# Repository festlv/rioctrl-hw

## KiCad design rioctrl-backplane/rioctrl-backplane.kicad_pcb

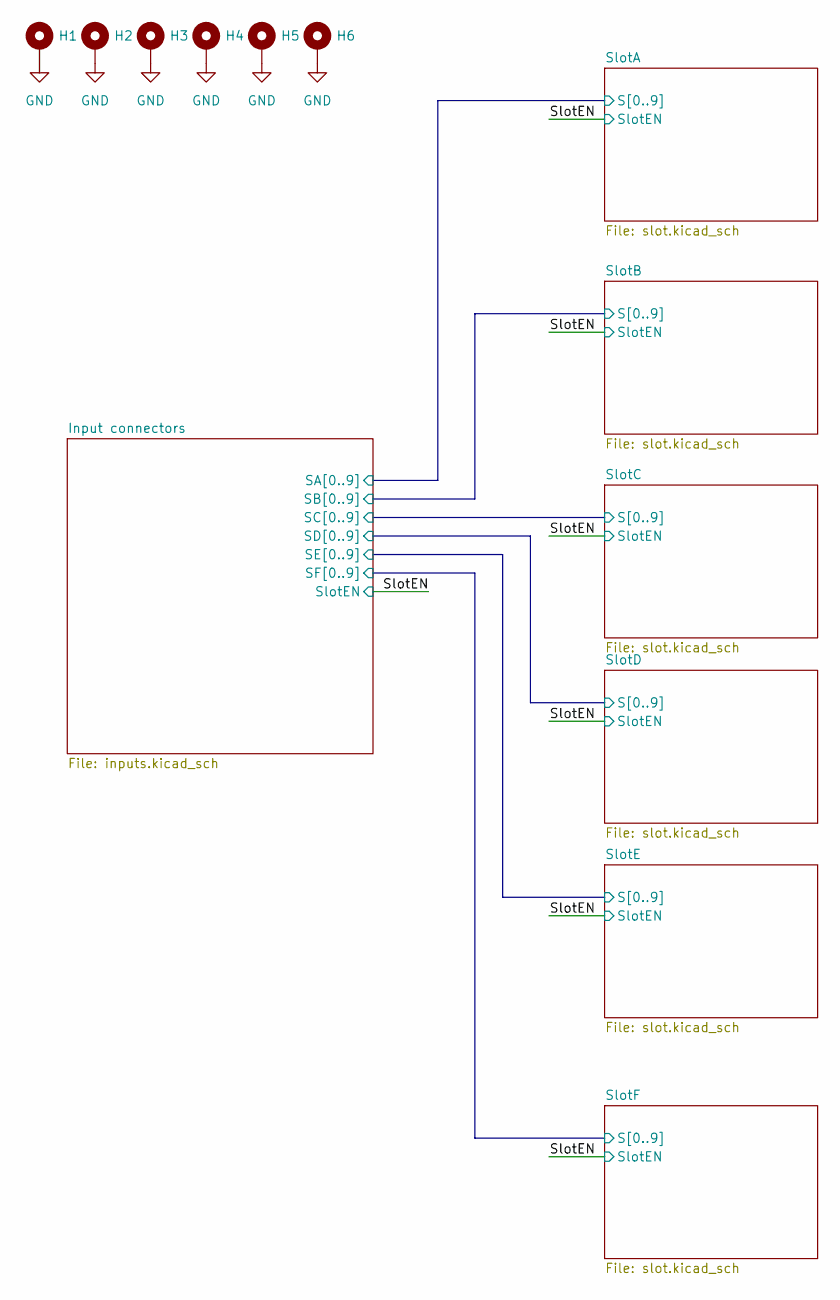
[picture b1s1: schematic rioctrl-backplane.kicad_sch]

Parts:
H1, H2, H3, H4, H5, H6: MH_3.2mm; MountingHole_3.2mm_M3_Pad_Via

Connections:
GND: H1.1, H2.1, H3.1, H4.1, H5.1, H6.1; also elsewhere on the board

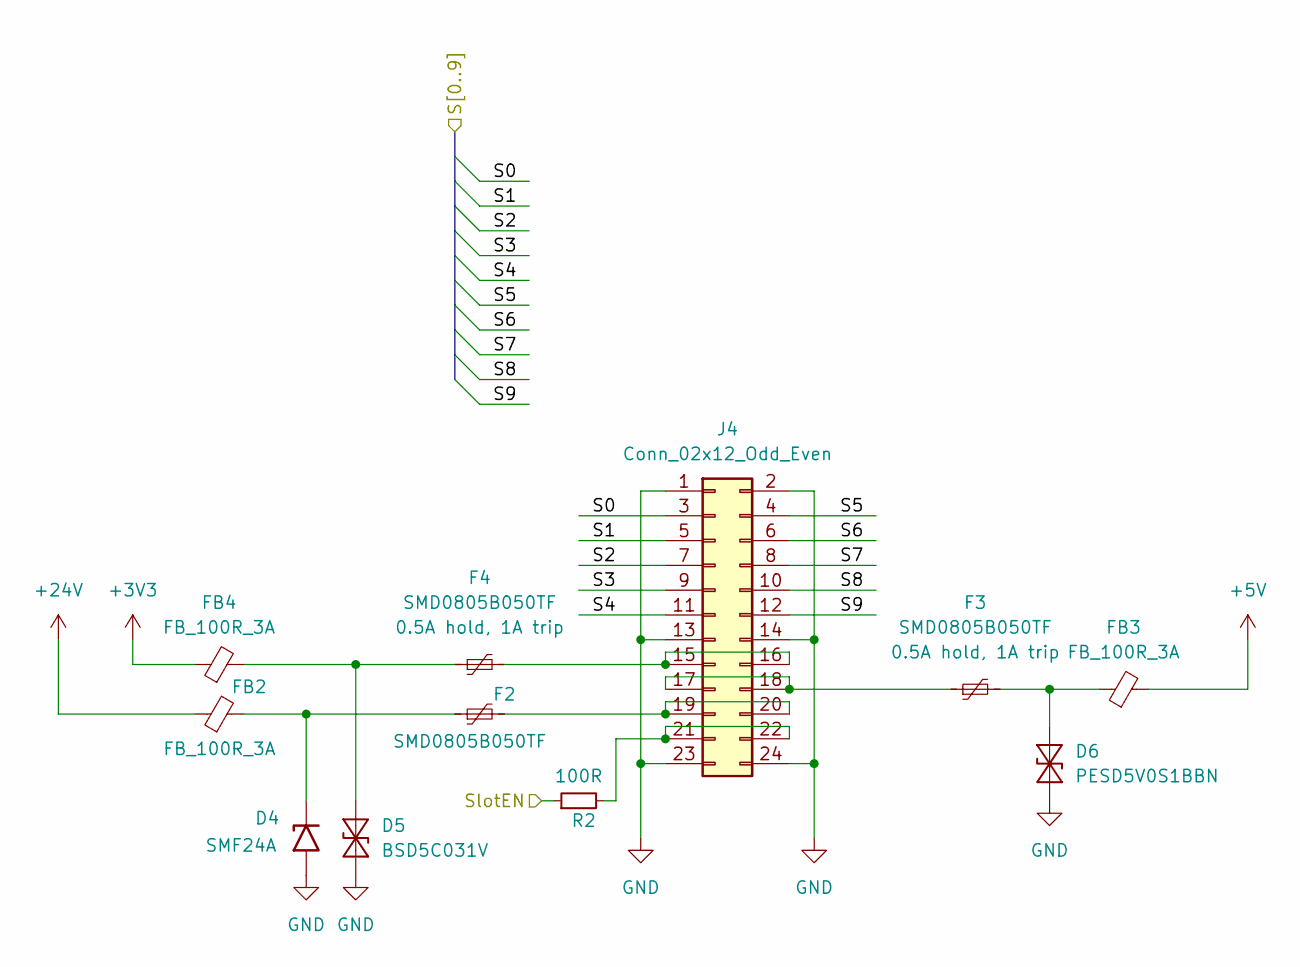
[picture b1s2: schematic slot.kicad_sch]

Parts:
D4: SMF24A; D_SOD-123F; MPN SMF24A; LCSC# C169430
D5: BSD5C031V; D_SOD-523; MPN BSD5C031V; LCSC# C151984
D6: PESD5V0S1BBN; D_SOD-523; MPN PESD5V0S1BBN; LCSC# C314264
F2, F3, F4: SMD0805B050TF; Fuse_0805_2012Metric; MPN SMD0805B050TF; LCSC# C269104
FB2, FB3, FB4: FB_100R_3A; L_0603_1608Metric; MPN UPZ1608E101-3R0TF; LCSC# C96995
J4: Conn_02x12_Odd_Even; PinSocket_2x12_P2.54mm_Vertical_SMD
R2: 100R; R_0603_1608Metric

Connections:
+3V3: FB4.1; also elsewhere on the board
+5V: FB3.2; also elsewhere on the board
+24V: FB2.1; also elsewhere on the board
/Input connectors/SB0: J4.3; also elsewhere on the board
/Input connectors/SB1: J4.5; also elsewhere on the board
/Input connectors/SB2: J4.7; also elsewhere on the board
/Input connectors/SB3: J4.9; also elsewhere on the board
/Input connectors/SB4: J4.11; also elsewhere on the board
/Input connectors/SB5: J4.4; also elsewhere on the board
/Input connectors/SB6: J4.6; also elsewhere on the board
/Input connectors/SB7: J4.8; also elsewhere on the board
/Input connectors/SB8: J4.10; also elsewhere on the board
/Input connectors/SB9: J4.12; also elsewhere on the board
/SlotEN: R2.1; also elsewhere on the board
GND: D4.2 (A2), D5.1 (A1), D6.2 (A2), J4.1, J4.2, J4.13, J4.14, J4.23, J4.24; also elsewhere on the board
unnamed: D5.2 (A2), F4.1, FB4.2
unnamed: F4.2, J4.15, J4.16
unnamed: J4.21, J4.22, R2.2

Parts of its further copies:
D1, D7, D10, D13, D16: SMF24A; D_SOD-123F; MPN SMF24A; LCSC# C169430
D2, D8, D11, D14, D17: BSD5C031V; D_SOD-523; MPN BSD5C031V; LCSC# C151984
D3, D9, D12, D15, D18: PESD5V0S1BBN; D_SOD-523; MPN PESD5V0S1BBN; LCSC# C314264
F1, F5, F6, F7, F8, F9, F10, F11, F12, F13, F14, F15, F16, F17, F18: SMD0805B050TF; Fuse_0805_2012Metric; MPN SMD0805B050TF; LCSC# C269104
FB1, FB5, FB6, FB7, FB8, FB9, FB10, FB11, FB12, FB13, FB14, FB15, FB16, FB17, FB18: FB_100R_3A; L_0603_1608Metric; MPN UPZ1608E101-3R0TF; LCSC# C96995
J3, J5, J6, J7, J8: Conn_02x12_Odd_Even; PinSocket_2x12_P2.54mm_Vertical_SMD
R1, R3, R4, R5, R6: 100R; R_0603_1608Metric

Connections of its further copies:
+3V3: FB1.1, FB7.1, FB10.1, FB13.1, FB16.1; also elsewhere on the board
+5V: FB6.2, FB9.2, FB12.2, FB15.2, FB18.2; also elsewhere on the board
+24V: FB5.1, FB8.1, FB11.1, FB14.1, FB17.1; also elsewhere on the board
/Input connectors/SA0: J3.3; also elsewhere on the board
/Input connectors/SA1: J3.5; also elsewhere on the board
/Input connectors/SA2: J3.7; also elsewhere on the board
/Input connectors/SA3: J3.9; also elsewhere on the board
/Input connectors/SA4: J3.11; also elsewhere on the board
/Input connectors/SA5: J3.4; also elsewhere on the board
/Input connectors/SA6: J3.6; also elsewhere on the board
/Input connectors/SA7: J3.8; also elsewhere on the board
/Input connectors/SA8: J3.10; also elsewhere on the board
/Input connectors/SA9: J3.12; also elsewhere on the board
/Input connectors/SC0: J5.3; also elsewhere on the board
/Input connectors/SC1: J5.5; also elsewhere on the board
/Input connectors/SC2: J5.7; also elsewhere on the board
/Input connectors/SC3: J5.9; also elsewhere on the board
/Input connectors/SC4: J5.11; also elsewhere on the board
/Input connectors/SC5: J5.4; also elsewhere on the board
/Input connectors/SC6: J5.6; also elsewhere on the board
/Input connectors/SC7: J5.8; also elsewhere on the board
/Input connectors/SC8: J5.10; also elsewhere on the board
/Input connectors/SC9: J5.12; also elsewhere on the board
/Input connectors/SD0: J6.3; also elsewhere on the board
/Input connectors/SD1: J6.5; also elsewhere on the board
/Input connectors/SD2: J6.7; also elsewhere on the board
/Input connectors/SD3: J6.9; also elsewhere on the board
/Input connectors/SD4: J6.11; also elsewhere on the board
/Input connectors/SD5: J6.4; also elsewhere on the board
/Input connectors/SD6: J6.6; also elsewhere on the board
/Input connectors/SD7: J6.8; also elsewhere on the board
/Input connectors/SD8: J6.10; also elsewhere on the board
/Input connectors/SD9: J6.12; also elsewhere on the board
/Input connectors/SE0: J7.3; also elsewhere on the board
/Input connectors/SE1: J7.5; also elsewhere on the board
/Input connectors/SE2: J7.7; also elsewhere on the board
/Input connectors/SE3: J7.9; also elsewhere on the board
/Input connectors/SE4: J7.11; also elsewhere on the board
/Input connectors/SE5: J7.4; also elsewhere on the board
/Input connectors/SE6: J7.6; also elsewhere on the board
/Input connectors/SE7: J7.8; also elsewhere on the board
/Input connectors/SE8: J7.10; also elsewhere on the board
/Input connectors/SE9: J7.12; also elsewhere on the board
/Input connectors/SF0: J8.3; also elsewhere on the board
/Input connectors/SF1: J8.5; also elsewhere on the board
/Input connectors/SF2: J8.7; also elsewhere on the board
/Input connectors/SF3: J8.9; also elsewhere on the board
/Input connectors/SF4: J8.11; also elsewhere on the board
/Input connectors/SF5: J8.4; also elsewhere on the board
/Input connectors/SF6: J8.6; also elsewhere on the board
/Input connectors/SF7: J8.8; also elsewhere on the board
/Input connectors/SF8: J8.10; also elsewhere on the board
/Input connectors/SF9: J8.12; also elsewhere on the board
/SlotEN: R1.1, R3.1, R4.1, R5.1, R6.1; also elsewhere on the board
GND: D1.2 (A2), D2.1 (A1), D3.2 (A2), D7.2 (A2), D8.1 (A1), D9.2 (A2), D10.2 (A2), D11.1 (A1), D12.2 (A2), D13.2 (A2), D14.1 (A1), D15.2 (A2), D16.2 (A2), D17.1 (A1), D18.2 (A2), J3.1, J3.2, J3.13, J3.14, J3.23, J3.24, J5.1, J5.2, J5.13, J5.14, J5.23, J5.24, J6.1, J6.2, J6.13, J6.14, J6.23, J6.24, J7.1, J7.2, J7.13, J7.14, J7.23, J7.24, J8.1, J8.2, J8.13, J8.14, J8.23, J8.24; also elsewhere on the board
unnamed: D2.2 (A2), F1.1, FB1.2
unnamed: D7.1 (A1), F8.1, FB8.2
unnamed: D8.2 (A2), F7.1, FB7.2
unnamed: D9.1 (A1), F9.2, FB9.1
unnamed: D10.1 (A1), F11.1, FB11.2
unnamed: D11.2 (A2), F10.1, FB10.2
unnamed: D12.1 (A1), F12.2, FB12.1
unnamed: D13.1 (A1), F14.1, FB14.2
unnamed: D14.2 (A2), F13.1, FB13.2
unnamed: D15.1 (A1), F15.2, FB15.1
unnamed: D16.1 (A1), F17.1, FB17.2
unnamed: D17.2 (A2), F16.1, FB16.2
unnamed: D18.1 (A1), F18.2, FB18.1
unnamed: F1.2, J3.15, J3.16
unnamed: J3.21, J3.22, R1.2
unnamed: F7.2, J5.15, J5.16
unnamed: F9.1, J5.17, J5.18
unnamed: F8.2, J5.19, J5.20
unnamed: J5.21, J5.22, R3.2
unnamed: F10.2, J6.15, J6.16
unnamed: F12.1, J6.17, J6.18
unnamed: F11.2, J6.19, J6.20
unnamed: J6.21, J6.22, R4.2
unnamed: F13.2, J7.15, J7.16
unnamed: F15.1, J7.17, J7.18
unnamed: F14.2, J7.19, J7.20
unnamed: J7.21, J7.22, R5.2
unnamed: F16.2, J8.15, J8.16
unnamed: F18.1, J8.17, J8.18
unnamed: F17.2, J8.19, J8.20
unnamed: J8.21, J8.22, R6.2

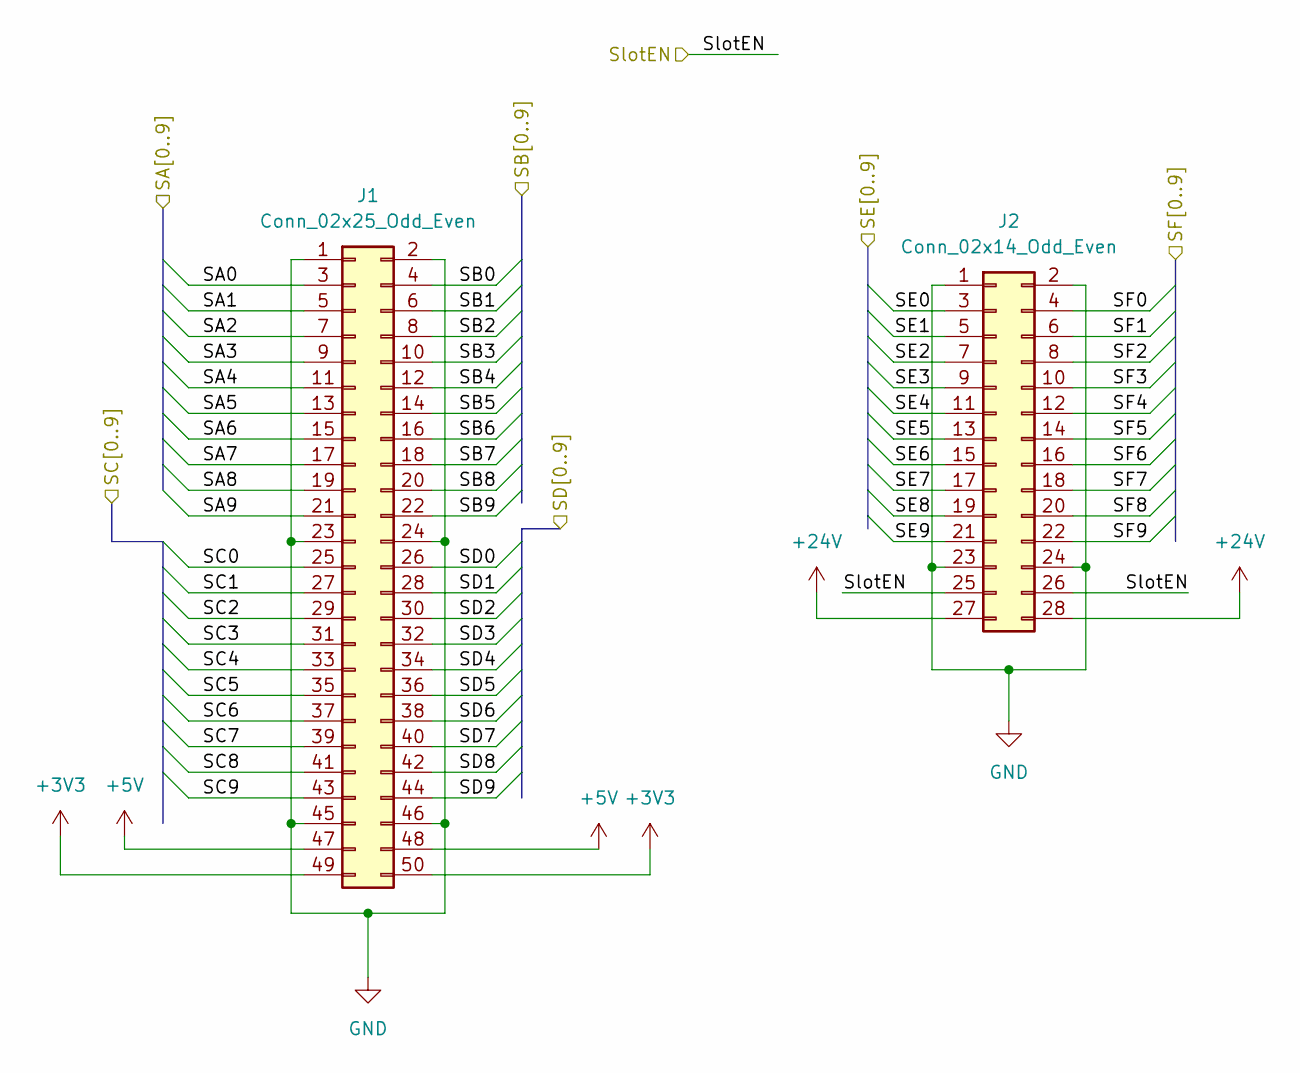
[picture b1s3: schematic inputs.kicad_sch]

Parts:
J1: Conn_02x25_Odd_Even; PinHeader_2x25_P2.54mm_Horizontal
J2: Conn_02x14_Odd_Even; PinHeader_2x14_P2.54mm_Horizontal

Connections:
+3V3: J1.49, J1.50; also elsewhere on the board
+5V: J1.47, J1.48; also elsewhere on the board
+24V: J2.27, J2.28; also elsewhere on the board
/Input connectors/SA0: J1.3; also elsewhere on the board
/Input connectors/SA1: J1.5; also elsewhere on the board
/Input connectors/SA2: J1.7; also elsewhere on the board
/Input connectors/SA3: J1.9; also elsewhere on the board
/Input connectors/SA4: J1.11; also elsewhere on the board
/Input connectors/SA5: J1.13; also elsewhere on the board
/Input connectors/SA6: J1.15; also elsewhere on the board
/Input connectors/SA7: J1.17; also elsewhere on the board
/Input connectors/SA8: J1.19; also elsewhere on the board
/Input connectors/SA9: J1.21; also elsewhere on the board
/Input connectors/SB0: J1.4; also elsewhere on the board
/Input connectors/SB1: J1.6; also elsewhere on the board
/Input connectors/SB2: J1.8; also elsewhere on the board
/Input connectors/SB3: J1.10; also elsewhere on the board
/Input connectors/SB4: J1.12; also elsewhere on the board
/Input connectors/SB5: J1.14; also elsewhere on the board
/Input connectors/SB6: J1.16; also elsewhere on the board
/Input connectors/SB7: J1.18; also elsewhere on the board
/Input connectors/SB8: J1.20; also elsewhere on the board
/Input connectors/SB9: J1.22; also elsewhere on the board
/Input connectors/SC0: J1.25; also elsewhere on the board
/Input connectors/SC1: J1.27; also elsewhere on the board
/Input connectors/SC2: J1.29; also elsewhere on the board
/Input connectors/SC3: J1.31; also elsewhere on the board
/Input connectors/SC4: J1.33; also elsewhere on the board
/Input connectors/SC5: J1.35; also elsewhere on the board
/Input connectors/SC6: J1.37; also elsewhere on the board
/Input connectors/SC7: J1.39; also elsewhere on the board
/Input connectors/SC8: J1.41; also elsewhere on the board
/Input connectors/SC9: J1.43; also elsewhere on the board
/Input connectors/SD0: J1.26; also elsewhere on the board
/Input connectors/SD1: J1.28; also elsewhere on the board
/Input connectors/SD2: J1.30; also elsewhere on the board
/Input connectors/SD3: J1.32; also elsewhere on the board
/Input connectors/SD4: J1.34; also elsewhere on the board
/Input connectors/SD5: J1.36; also elsewhere on the board
/Input connectors/SD6: J1.38; also elsewhere on the board
/Input connectors/SD7: J1.40; also elsewhere on the board
/Input connectors/SD8: J1.42; also elsewhere on the board
/Input connectors/SD9: J1.44; also elsewhere on the board
/Input connectors/SE0: J2.3; also elsewhere on the board
/Input connectors/SE1: J2.5; also elsewhere on the board
/Input connectors/SE2: J2.7; also elsewhere on the board
/Input connectors/SE3: J2.9; also elsewhere on the board
/Input connectors/SE4: J2.11; also elsewhere on the board
/Input connectors/SE5: J2.13; also elsewhere on the board
/Input connectors/SE6: J2.15; also elsewhere on the board
/Input connectors/SE7: J2.17; also elsewhere on the board
/Input connectors/SE8: J2.19; also elsewhere on the board
/Input connectors/SE9: J2.21; also elsewhere on the board
/Input connectors/SF0: J2.4; also elsewhere on the board
/Input connectors/SF1: J2.6; also elsewhere on the board
/Input connectors/SF2: J2.8; also elsewhere on the board
/Input connectors/SF3: J2.10; also elsewhere on the board
/Input connectors/SF4: J2.12; also elsewhere on the board
/Input connectors/SF5: J2.14; also elsewhere on the board
/Input connectors/SF6: J2.16; also elsewhere on the board
/Input connectors/SF7: J2.18; also elsewhere on the board
/Input connectors/SF8: J2.20; also elsewhere on the board
/Input connectors/SF9: J2.22; also elsewhere on the board
/SlotEN: J2.25, J2.26; also elsewhere on the board
GND: J1.1, J1.2, J1.23, J1.24, J1.45, J1.46, J2.1, J2.2, J2.23, J2.24; also elsewhere on the board

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
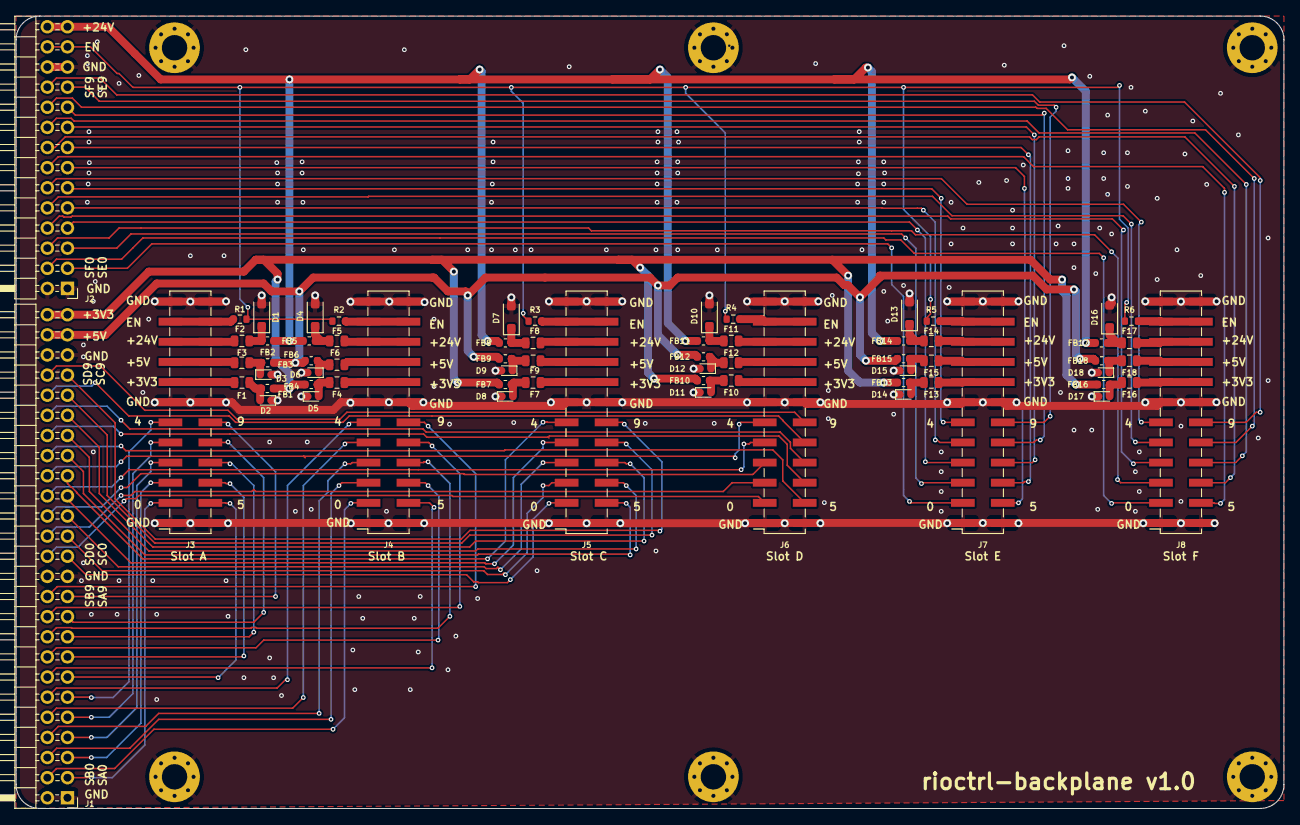
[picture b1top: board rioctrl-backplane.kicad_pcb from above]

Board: 2 copper layers, 160.0 x 100.0 mm, 74 parts (0 on the bottom side), 107 nets.
